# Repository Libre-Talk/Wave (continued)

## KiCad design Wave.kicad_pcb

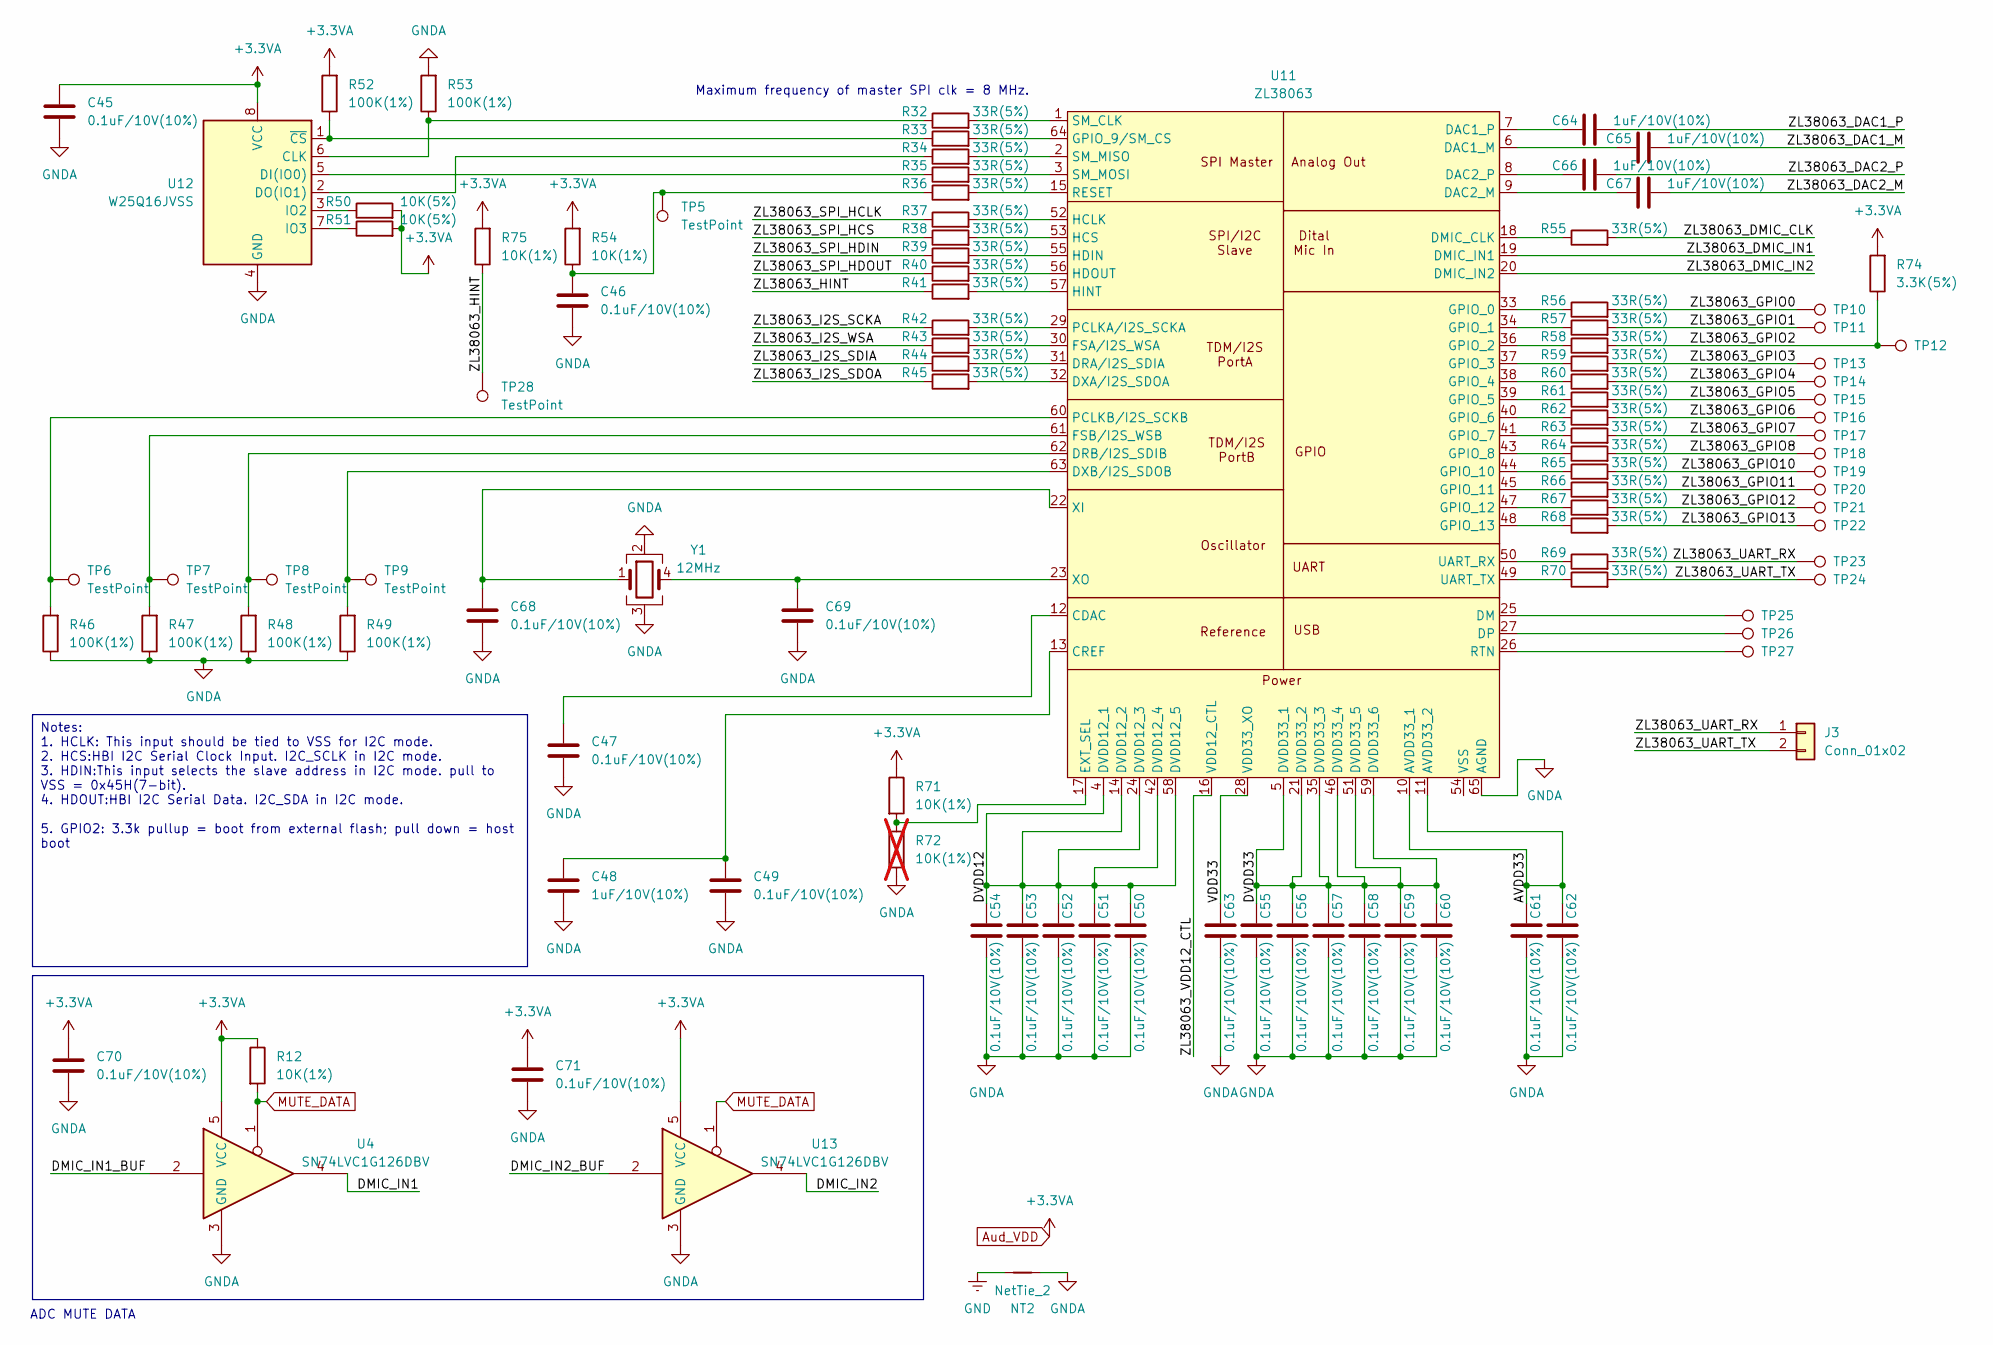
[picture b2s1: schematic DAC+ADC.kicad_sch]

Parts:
C45, C46, C47, C49, C50, C51, C52, C53, C54, C55, C56, C57, C58, C59, C60, C61, C62, C63, C68, C69, C70, C71: 0.1uF/10V(10%); C_0402_1005Metric
C48, C64, C65, C66, C67: 1uF/10V(10%); C_0402_1005Metric
J3: Conn_01x02; PinHeader_1x02_P2.54mm_Vertical
NT2: NetTie_2; NetTie-2_SMD_Pad0.5mm
R12, R54, R71, R75: 10K(1%); R_0402_1005Metric
R32, R33, R34, R35, R36, R37, R38, R39, R40, R41, R42, R43, R44, R45, R55, R56, R57, R58, R59, R60, R61, R62, R63, R64, R65, R66, R67, R68, R69, R70: 33R(5%); R_0402_1005Metric
R46, R47, R48, R49, R52, R53: 100K(1%); R_0402_1005Metric
R50, R51: 10K(5%); R_0402_1005Metric
R72: 10K(1%); R_0402_1005Metric; not fitted
R74: 3.3K(5%); R_0402_1005Metric
TP5, TP6, TP7, TP8, TP9, TP10, TP11, TP12, TP13, TP14, TP15, TP16, TP17, TP18, TP19, TP20, TP21, TP22, TP23, TP24, TP25, TP26, TP27, TP28: TestPoint; TestPoint_Pad_D1.0mm
U4, U13: SN74LVC1G126DBV; SOT-23-5
U11: ZL38063; QFN-64-1EP_9x9mm_P0.5mm_EP7.3x7.3mm_ThermalVias
U12: W25Q16JVSS; SOIC-8_3.9x4.9mm_P1.27mm
Y1: 12MHz; Crystal_SMD_2520-4Pin_2.5x2.0mm

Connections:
/DAC+ADC/AVDD33: C61.1, C62.1, U11.10 (AVDD33_1), U11.11 (AVDD33_2)
/DAC+ADC/DMIC_IN1: U4.4
/DAC+ADC/DMIC_IN1_BUF: U4.2
/DAC+ADC/DMIC_IN2: U13.4
/DAC+ADC/DMIC_IN2_BUF: U13.2
/DAC+ADC/DVDD12: C50.1, C51.1, C52.1, C53.1, C54.1, U11.4 (DVDD12_1), U11.14 (DVDD12_2), U11.24 (DVDD12_3), U11.42 (DVDD12_4), U11.58 (DVDD12_5)
/DAC+ADC/DVDD33: C55.1, C56.1, C57.1, C58.1, C59.1, C60.1, U11.5 (DVDD33_1), U11.21 (DVDD33_2), U11.35 (DVDD33_3), U11.46 (DVDD33_4), U11.51 (DVDD33_5), U11.59 (DVDD33_6)
/DAC+ADC/VDD33: C63.1, U11.28 (VDD33_XO)
/DAC+ADC/ZL38063_DAC1_M: C65.2
/DAC+ADC/ZL38063_DAC1_P: C64.2
/DAC+ADC/ZL38063_DAC2_M: C67.2
/DAC+ADC/ZL38063_DAC2_P: C66.2
/DAC+ADC/ZL38063_DMIC_CLK: R55.2
/DAC+ADC/ZL38063_DMIC_IN1: U11.19 (DMIC_IN1)
/DAC+ADC/ZL38063_DMIC_IN2: U11.20 (DMIC_IN2)
/DAC+ADC/ZL38063_GPIO0: R56.2, TP10.1
/DAC+ADC/ZL38063_GPIO1: R57.2, TP11.1
/DAC+ADC/ZL38063_GPIO2: R58.2, R74.1, TP12.1
/DAC+ADC/ZL38063_GPIO3: R59.2, TP13.1
/DAC+ADC/ZL38063_GPIO4: R60.2, TP14.1
/DAC+ADC/ZL38063_GPIO5: R61.2, TP15.1
/DAC+ADC/ZL38063_GPIO6: R62.2, TP16.1
/DAC+ADC/ZL38063_GPIO7: R63.2, TP17.1
/DAC+ADC/ZL38063_GPIO8: R64.2, TP18.1
/DAC+ADC/ZL38063_GPIO10: R65.2, TP19.1
/DAC+ADC/ZL38063_GPIO11: R66.2, TP20.1
/DAC+ADC/ZL38063_GPIO12: R67.2, TP21.1
/DAC+ADC/ZL38063_GPIO13: R68.2, TP22.1
/DAC+ADC/ZL38063_HINT: R41.1, R75.1, TP28.1
/DAC+ADC/ZL38063_I2S_SCKA: R42.1
/DAC+ADC/ZL38063_I2S_SDIA: R44.1
/DAC+ADC/ZL38063_I2S_SDOA: R45.1
/DAC+ADC/ZL38063_I2S_WSA: R43.1
/DAC+ADC/ZL38063_SPI_HCLK: R37.1
/DAC+ADC/ZL38063_SPI_HCS: R38.1
/DAC+ADC/ZL38063_SPI_HDIN: R39.1
/DAC+ADC/ZL38063_SPI_HDOUT: R40.1
/DAC+ADC/ZL38063_UART_RX: J3.1, R69.2, TP23.1
/DAC+ADC/ZL38063_UART_TX: J3.2, R70.2, TP24.1
/DAC+ADC/ZL38063_VDD12_CTL: U11.16 (VDD12_CTL)
Aud_VDD: C45.1, C70.1, C71.1, R12.1, R50.2, R51.2, R52.2, R54.2, R71.1, R74.2, R75.2, U4.5 (VCC), U12.8 (VCC), U13.5 (VCC); also elsewhere on the board
GND: NT2.2; also elsewhere on the board
GNDA: C45.2, C46.2, C47.2, C48.2, C49.2, C50.2, C51.2, C52.2, C53.2, C54.2, C55.2, C56.2, C57.2, C58.2, C59.2, C60.2, C61.2, C62.2, C63.2, C68.2, C69.2, C70.2, C71.2, NT2.1, R46.1, R47.1, R48.1, R49.1, R53.2, R72.2, U4.3 (GND), U11.65 (AGND), U12.4 (GND), U13.3 (GND), Y1.2, Y1.3
MUTE_DATA: R12.2, U4.1, U13.1; also elsewhere on the board
unnamed: C46.1, R36.1, R54.1, TP5.1
unnamed: C47.1, U11.12 (CDAC)
unnamed: C48.1, C49.1, U11.13 (CREF)
unnamed: C65.1, U11.6 (DAC1_M)
unnamed: C64.1, U11.7 (DAC1_P)
unnamed: C67.1, U11.9 (DAC2_M)
unnamed: C66.1, U11.8 (DAC2_P)
unnamed: TP25.1, U11.25 (DM)
unnamed: R55.1, U11.18 (DMIC_CLK)
unnamed: TP26.1, U11.27 (DP)
unnamed: R44.2, U11.31 (DRA/I2S_SDIA)
unnamed: R48.2, TP8.1, U11.62 (DRB/I2S_SDIB)
unnamed: R45.2, U11.32 (DXA/I2S_SDOA)
unnamed: R49.2, TP9.1, U11.63 (DXB/I2S_SDOB)
unnamed: R71.2, R72.1, U11.17 (EXT_SEL)
unnamed: R43.2, U11.30 (FSA/I2S_WSA)
unnamed: R47.2, TP7.1, U11.61 (FSB/I2S_WSB)
unnamed: R56.1, U11.33 (GPIO_0)
unnamed: R57.1, U11.34 (GPIO_1)
unnamed: R58.1, U11.36 (GPIO_2)
unnamed: R59.1, U11.37 (GPIO_3)
unnamed: R60.1, U11.38 (GPIO_4)
unnamed: R61.1, U11.39 (GPIO_5)
unnamed: R62.1, U11.40 (GPIO_6)
unnamed: R63.1, U11.41 (GPIO_7)
unnamed: R64.1, U11.43 (GPIO_8)
unnamed: R33.2, U11.64 (GPIO_9/SM_CS)
unnamed: R65.1, U11.44 (GPIO_10)
unnamed: R66.1, U11.45 (GPIO_11)
unnamed: R67.1, U11.47 (GPIO_12)
unnamed: R68.1, U11.48 (GPIO_13)
unnamed: R37.2, U11.52 (HCLK)
unnamed: R38.2, U11.53 (HCS)
unnamed: R39.2, U11.55 (HDIN)
unnamed: R40.2, U11.56 (HDOUT)
unnamed: R41.2, U11.57 (HINT)
unnamed: R42.2, U11.29 (PCLKA/I2S_SCKA)
unnamed: R46.2, TP6.1, U11.60 (PCLKB/I2S_SCKB)
unnamed: R36.2, U11.15 (RESET)
unnamed: TP27.1, U11.26 (RTN)
unnamed: R32.2, U11.1 (SM_CLK)
unnamed: R34.2, U11.2 (SM_MISO)
unnamed: R35.2, U11.3 (SM_MOSI)
unnamed: R69.1, U11.50 (UART_RX)
unnamed: R70.1, U11.49 (UART_TX)
unnamed: C68.1, U11.22 (XI), Y1.1
unnamed: C69.1, U11.23 (XO), Y1.4
unnamed: R32.1, R53.1, U12.6 (CLK)
unnamed: R35.1, U12.5 (DI(IO0))
unnamed: R34.1, U12.2 (DO(IO1))
unnamed: R50.1, U12.3 (IO2)
unnamed: R51.1, U12.7 (IO3)
unnamed: R33.1, R52.1, U12.1 (~CS)

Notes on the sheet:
Notes: 1. HCLK: This input should be tied to VSS for I2C mode. 2. HCS:HBI I2C Serial Clock Input. I2C_SCLK in I2C mode. 3. HDIN:This input selects the slave address in I2C mode. pull to VSS = 0x45H(7-bit). 4. HDOUT:HBI I2C Serial Data. I2C_SDA in I2C mode. 5. GPIO2: 3.3k pullup = boot from external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
Maximum frequency of master SPI clk = 8 MHz.
ADC MUTE DATA

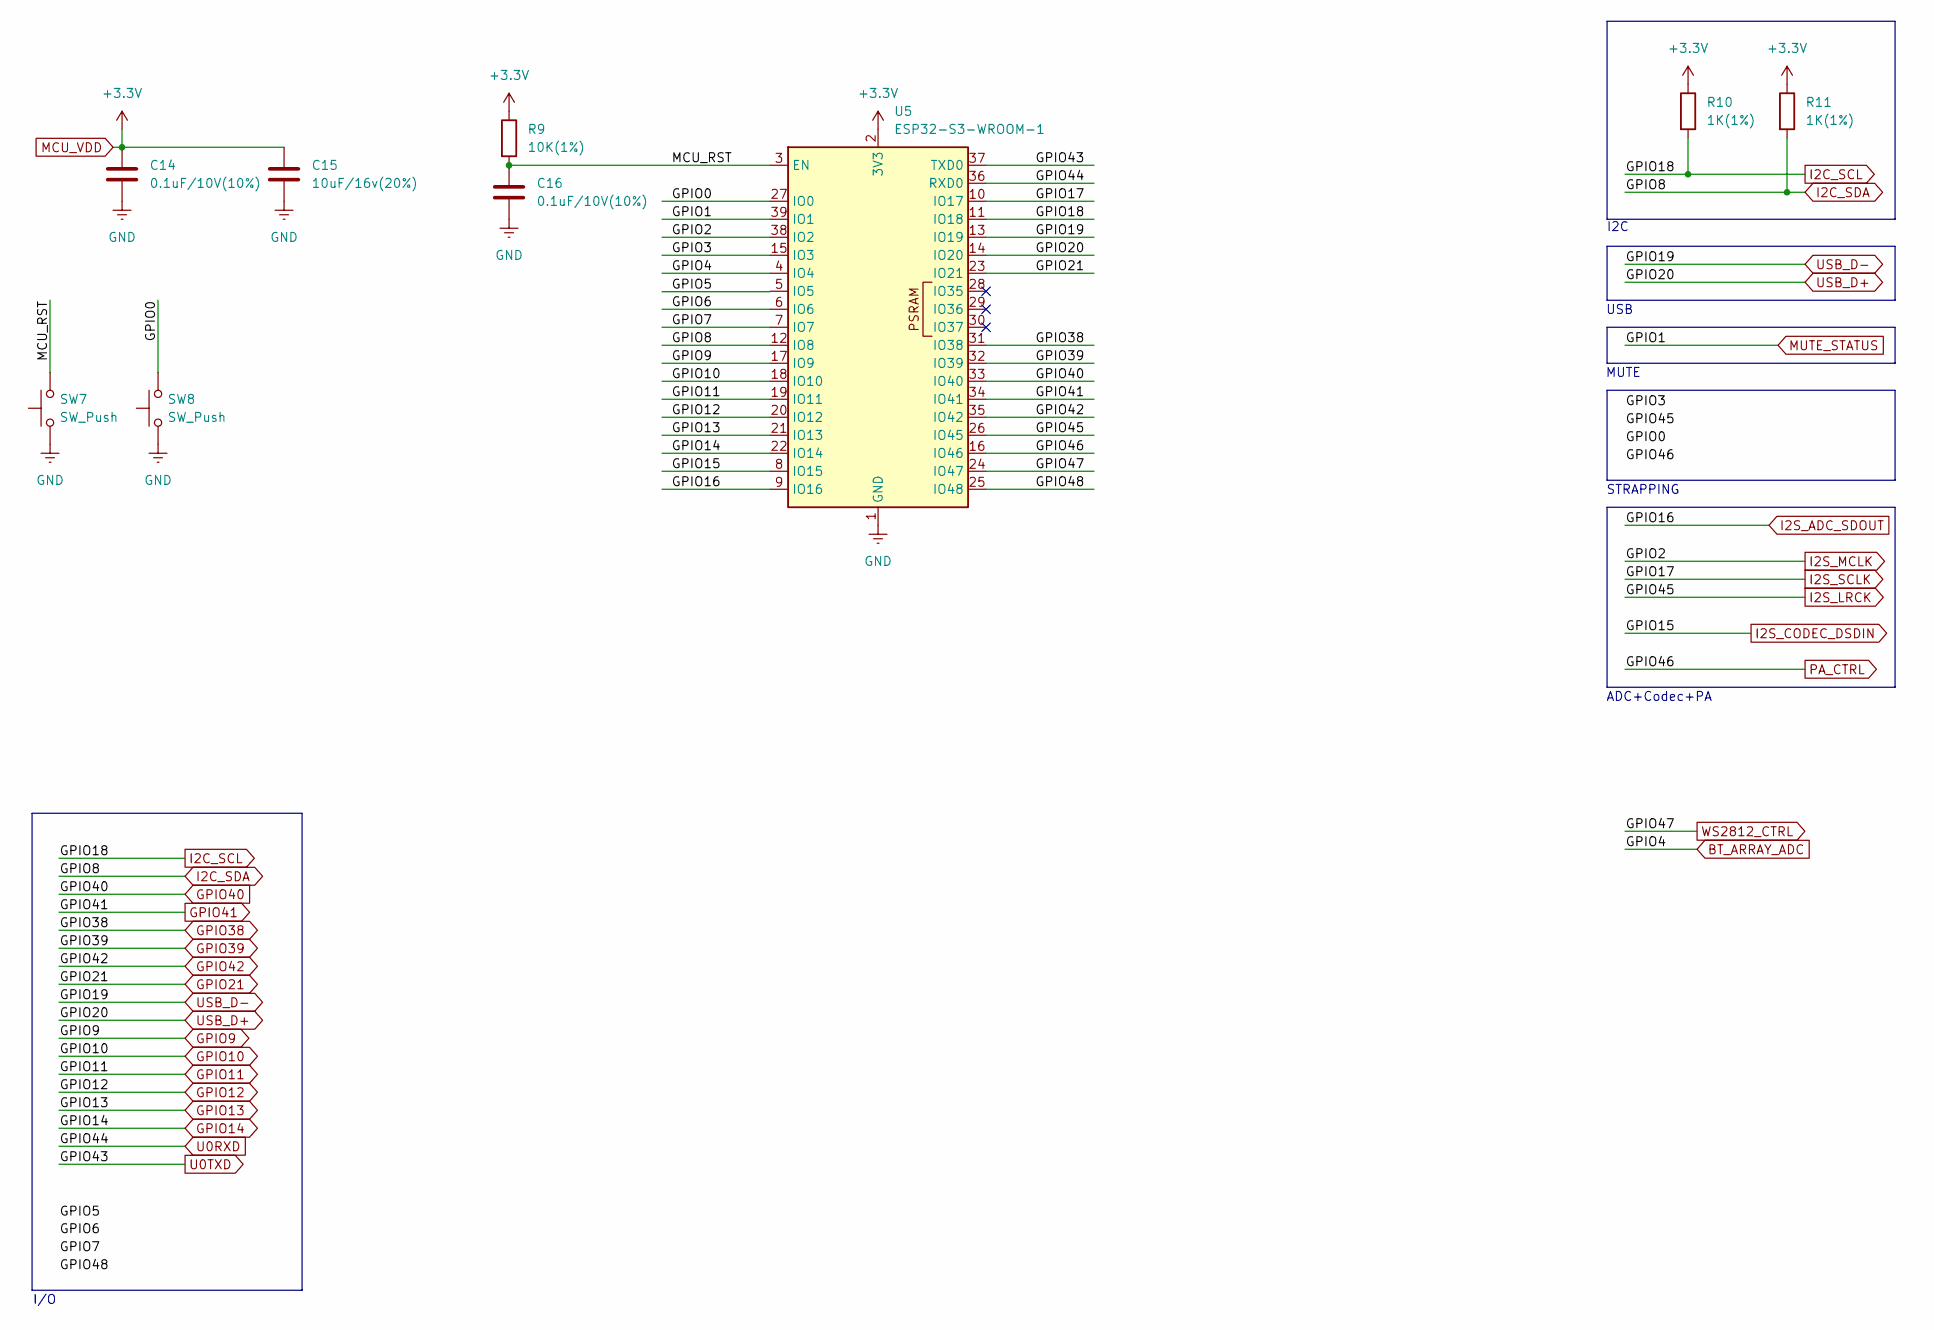
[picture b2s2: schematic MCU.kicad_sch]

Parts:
C14, C16: 0.1uF/10V(10%); C_0402_1005Metric
C15: 10uF/16v(20%); C_0402_1005Metric
R9: 10K(1%); R_0402_1005Metric
R10, R11: 1K(1%); R_0402_1005Metric
SW7, SW8: SW_Push; SW_SPST_PTS645
U5: ESP32-S3-WROOM-1

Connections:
/MCU/GPIO0: SW8.2, U5.27 (IO0)
/MCU/GPIO3: U5.15 (IO3)
/MCU/GPIO6: U5.6 (IO6)
/MCU/GPIO7: U5.7 (IO7)
/MCU/GPIO48: U5.25 (IO48)
/MCU/MCU_RST: C16.1, R9.2, SW7.2, U5.3 (EN)
BT_ARRAY_ADC: U5.4 (IO4); also elsewhere on the board
GND: C14.2, C15.2, C16.2, SW7.1, SW8.1, U5.1 (GND), U5.40 (GND), U5.41 (GND); also elsewhere on the board
GPIO9: U5.17 (IO9)
GPIO10: U5.18 (IO10)
GPIO11: U5.19 (IO11)
GPIO12: U5.20 (IO12)
GPIO13: U5.21 (IO13)
GPIO14: U5.22 (IO14)
GPIO21: U5.23 (IO21)
GPIO38: U5.31 (IO38)
GPIO39: U5.32 (IO39)
GPIO40: U5.33 (IO40)
GPIO41: U5.34 (IO41)
GPIO42: U5.35 (IO42)
I2C_SCL: R10.2, U5.11 (IO18); also elsewhere on the board
I2C_SDA: R11.2, U5.12 (IO8); also elsewhere on the board
I2S_ADC_SDOUT: U5.9 (IO16)
I2S_CODEC_DSDIN: U5.8 (IO15)
I2S_LRCK: U5.26 (IO45)
I2S_MCLK: U5.38 (IO2)
I2S_SCLK: U5.10 (IO17)
MCU_VDD: C14.1, C15.1, R9.1, R10.1, R11.1, U5.2 (3V3); also elsewhere on the board
MUTE_DATA: U5.39 (IO1); also elsewhere on the board
PA_CTRL: U5.16 (IO46); also elsewhere on the board
U0RXD: U5.36 (RXD0)
U0TXD: U5.37 (TXD0)
USB_D+: U5.14 (IO20); also elsewhere on the board
USB_D-: U5.13 (IO19); also elsewhere on the board
WS2812_CTRL: U5.24 (IO47); also elsewhere on the board

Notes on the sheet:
MUTE
ADC+Codec+PA
I/O
USB
STRAPPING
I2C

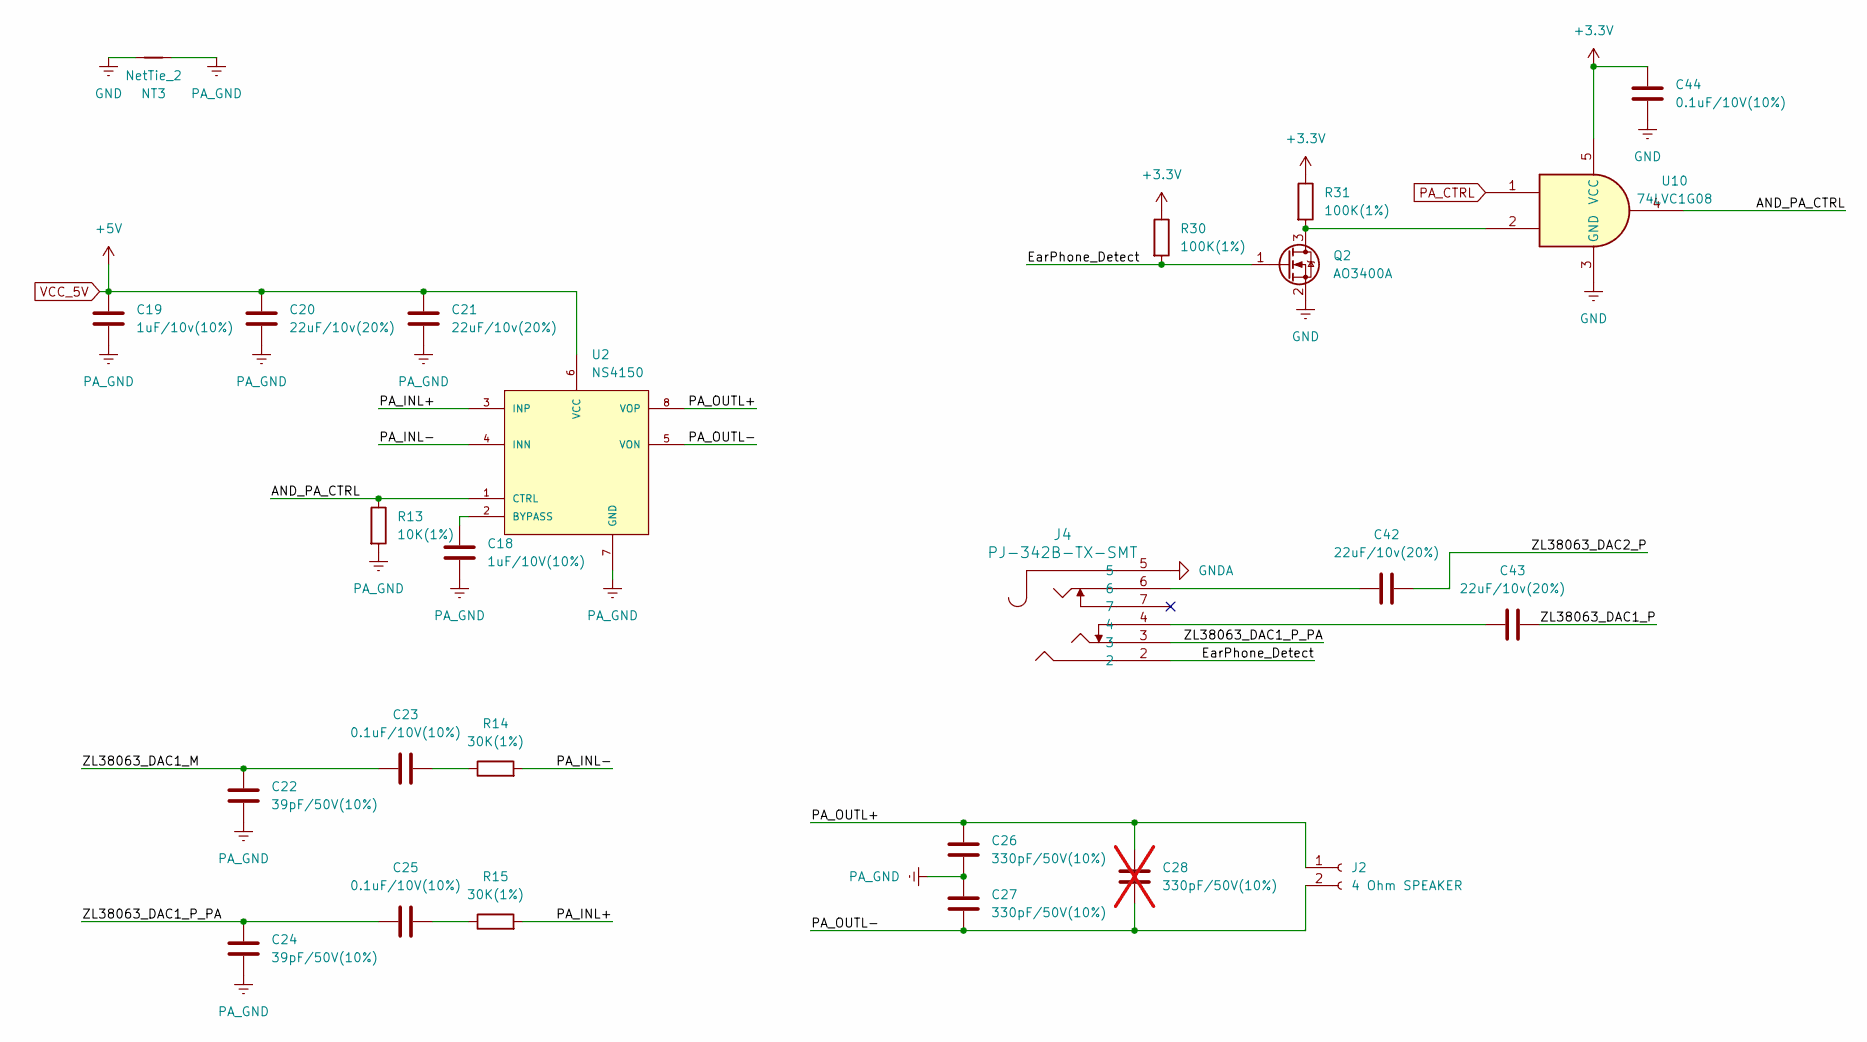
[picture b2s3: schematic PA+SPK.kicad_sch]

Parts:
C18: 1uF/10V(10%); C_0402_1005Metric
C19: 1uF/10v(10%); C_0402_1005Metric
C20, C21, C42, C43: 22uF/10v(20%); C_0402_1005Metric
C22, C24: 39pF/50V(10%); C_0402_1005Metric
C23, C25, C44: 0.1uF/10V(10%); C_0402_1005Metric
C26, C27: 330pF/50V(10%); C_0402_1005Metric
C28: 330pF/50V(10%); C_0402_1005Metric; not fitted
J2: 4 Ohm SPEAKER; JST_PH_B2B-PH-K_1x02_P2.00mm_Vertical
J4: PJ-342B-TX-SMT; PJ-342B-TX-SMT_XKB
NT3: NetTie_2; NetTie-2_SMD_Pad0.5mm
Q2: AO3400A; SOT-23
R13: 10K(1%); R_0402_1005Metric
R14, R15: 30K(1%); R_0402_1005Metric
R30, R31: 100K(1%); R_0402_1005Metric
U2: NS4150; MSOP-8_3x3mm_P0.65mm
U10: 74LVC1G08; SOT-23-5

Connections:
/PA & Speaker/AND_PA_CTRL: R13.1, U2.1 (CTRL), U10.4
/PA & Speaker/EarPhone_Detect: J4.2, Q2.1 (G), R30.2
/PA & Speaker/PA_INL+: R15.2, U2.3 (INP)
/PA & Speaker/PA_INL-: R14.2, U2.4 (INN)
/PA & Speaker/PA_OUTL+: C26.1, C28.1, J2.1, U2.8 (VOP)
/PA & Speaker/PA_OUTL-: C27.2, C28.2, J2.2, U2.5 (VON)
/PA & Speaker/ZL38063_DAC1_M: C22.1, C23.1
/PA & Speaker/ZL38063_DAC1_P: C43.2
/PA & Speaker/ZL38063_DAC1_P_PA: C24.1, C25.1, J4.3
/PA & Speaker/ZL38063_DAC2_P: C42.2
GND: C44.1, NT3.2, Q2.2 (S), U10.3 (GND); also elsewhere on the board
MCU_VDD: C44.2, R30.1, R31.1, U10.5 (VCC); also elsewhere on the board
unnamed: C23.2, R14.1
unnamed: C25.2, R15.1
unnamed: C42.1, J4.6
unnamed: C43.1, J4.4
unnamed: Q2.3 (D), R31.2, U10.2
unnamed: C18.1, U2.2 (BYPASS)
PA_CTRL: U10.1; also elsewhere on the board
PA_GND: C18.2, C19.2, C20.2, C21.2, C22.2, C24.2, C26.2, C27.1, NT3.1, R13.2, U2.7 (GND)
VCC_5V: C19.1, C20.1, C21.1, U2.6 (VCC); also elsewhere on the board

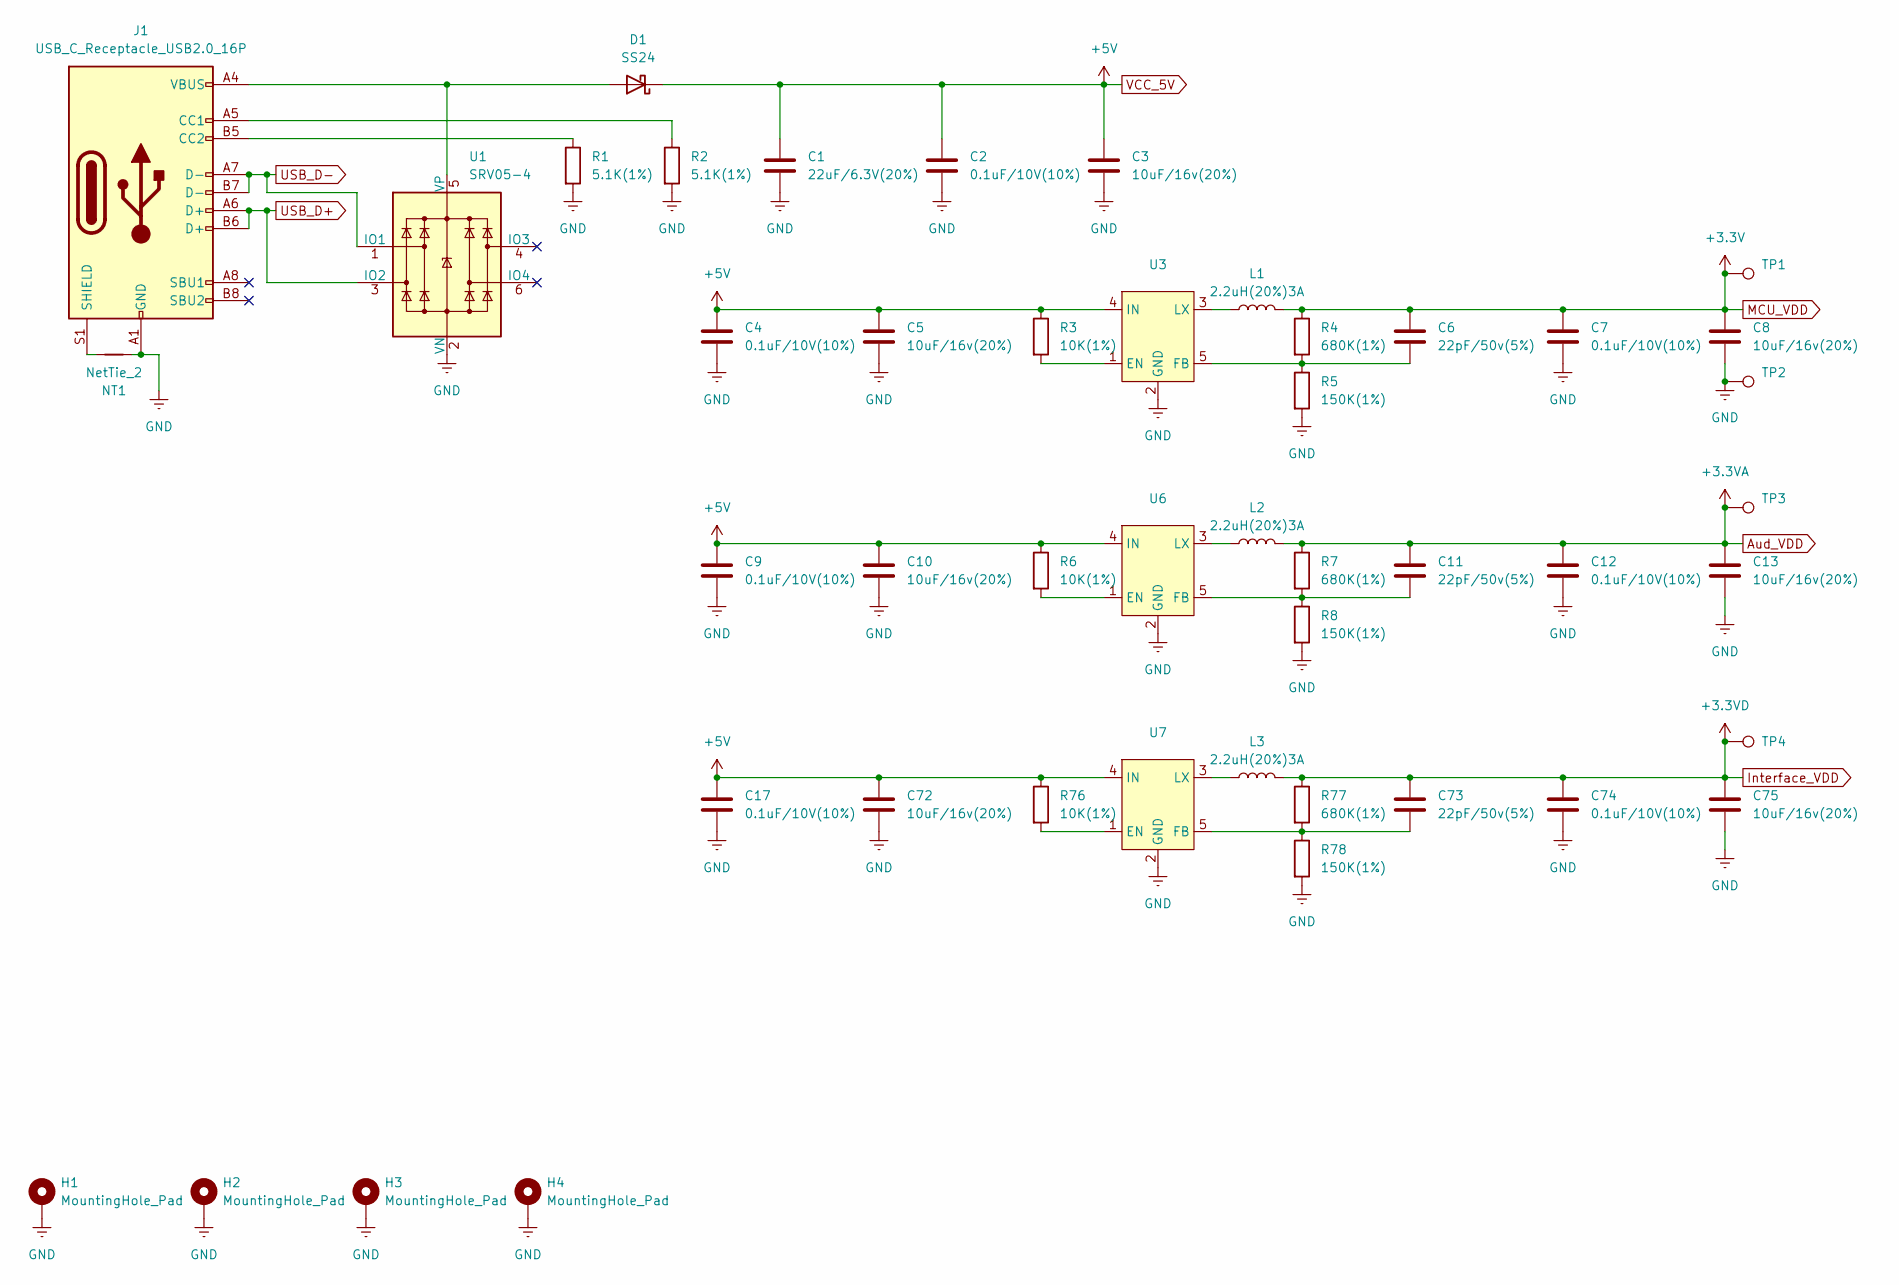
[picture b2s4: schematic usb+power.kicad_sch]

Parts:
C1: 22uF/6.3V(20%); C_0402_1005Metric
C2, C4, C7, C9, C12, C17, C74: 0.1uF/10V(10%); C_0402_1005Metric
C3, C5, C8, C10, C13, C72, C75: 10uF/16v(20%); C_0402_1005Metric
C6, C11, C73: 22pF/50v(5%); C_0402_1005Metric
D1: SS24; D_SMA
H1, H2, H3, H4: MountingHole_Pad; MountingHole_3.2mm_M3_Pad_Via
J1: USB_C_Receptacle_USB2.0_16P; USB_C_Receptacle_G-Switch_GT-USB-7010ASV
L1, L2, L3: 2.2uH(20%)3A; L_0603_1608Metric
NT1: NetTie_2; NetTie-2_SMD_Pad0.5mm
R1, R2: 5.1K(1%); R_0402_1005Metric
R3, R6, R76: 10K(1%); R_0402_1005Metric
R4, R7, R77: 680K(1%); R_0402_1005Metric
R5, R8, R78: 150K(1%); R_0402_1005Metric
TP1, TP2, TP3, TP4: TestPoint; TestPoint_Pad_D1.0mm
U1: SRV05-4; SOT-23-6
U3, U6, U7: SOT-23-5

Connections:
Aud_VDD: C11.1, C12.1, C13.1, L2.2, R7.1, TP3.1; also elsewhere on the board
GND: C1.2, C2.2, C3.2, C4.2, C5.2, C7.2, C8.2, C9.2, C10.2, C12.2, C13.2, C17.2, C72.2, C74.2, C75.2, H1.1, H2.1, H3.1, H4.1, J1.A1 (GND), J1.A12 (GND), J1.B1 (GND), J1.B12 (GND), NT1.1, R1.2, R2.2, R5.2, R8.2, R78.2, TP2.1, U1.2 (VN), U3.2 (GND), U6.2 (GND), U7.2 (GND); also elsewhere on the board
Interface_VDD: C73.1, C74.1, C75.1, L3.2, R77.1, TP4.1; also elsewhere on the board
MCU_VDD: C6.1, C7.1, C8.1, L1.2, R4.1, TP1.1; also elsewhere on the board
unnamed: D1.2 (A), J1.A4 (VBUS), J1.A9 (VBUS), J1.B4 (VBUS), J1.B9 (VBUS), U1.5 (VP)
unnamed: J1.A5 (CC1), R2.1
unnamed: J1.B5 (CC2), R1.1
unnamed: J1.S1 (SHIELD), NT1.2
unnamed: R3.2, U3.1 (EN)
unnamed: C6.2, R4.2, R5.1, U3.5 (FB)
unnamed: L1.1, U3.3 (LX)
unnamed: R6.2, U6.1 (EN)
unnamed: C11.2, R7.2, R8.1, U6.5 (FB)
unnamed: L2.1, U6.3 (LX)
unnamed: R76.2, U7.1 (EN)
unnamed: C73.2, R77.2, R78.1, U7.5 (FB)
unnamed: L3.1, U7.3 (LX)
USB_D+: J1.A6 (D+), J1.B6 (D+), U1.3 (IO2); also elsewhere on the board
USB_D-: J1.A7 (D-), J1.B7 (D-), U1.1 (IO1); also elsewhere on the board
VCC_5V: C1.1, C2.1, C3.1, C4.1, C5.1, C9.1, C10.1, C17.1, C72.1, D1.1 (K), R3.1, R6.1, R76.1, U3.4 (IN), U6.4 (IN), U7.4 (IN); also elsewhere on the board

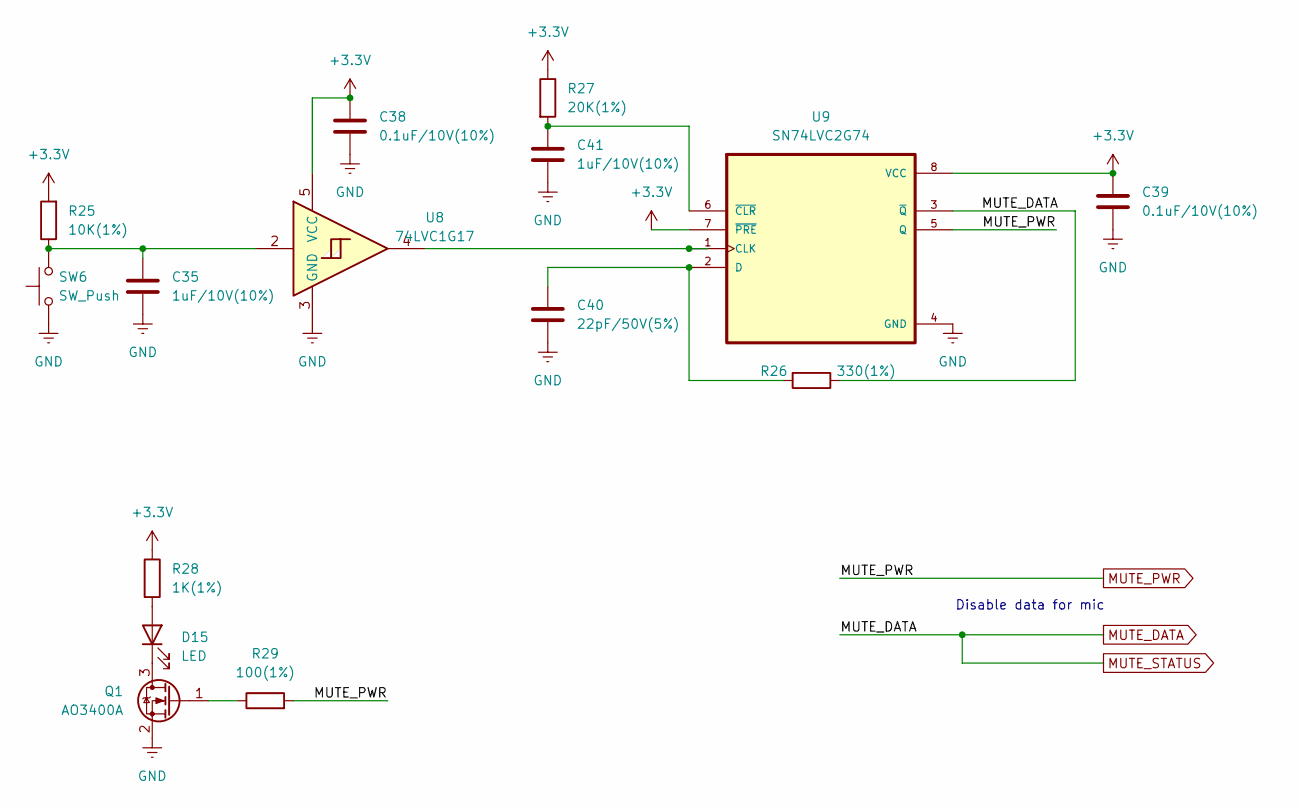
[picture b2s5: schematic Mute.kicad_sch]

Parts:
C35, C41: 1uF/10V(10%); C_0402_1005Metric
C38, C39: 0.1uF/10V(10%); C_0402_1005Metric
C40: 22pF/50V(5%); C_0402_1005Metric
D15: LED; LED_0603_1608Metric
Q1: AO3400A; SOT-23
R25: 10K(1%); R_0402_1005Metric
R26: 330(1%); R_0402_1005Metric
R27: 20K(1%); R_0402_1005Metric
R28: 1K(1%); R_0402_1005Metric
R29: 100(1%); R_0402_1005Metric
SW6: SW_Push; SW_SPST_PTS645
U8: 74LVC1G17; SOT-23-5
U9: SN74LVC2G74; VSSOP-8_2.4x2.1mm_P0.5mm

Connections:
GND: C35.2, C38.2, C39.2, C40.2, C41.2, Q1.2 (S), SW6.1, U8.3 (GND), U9.4 (GND); also elsewhere on the board
MCU_VDD: C38.1, C39.1, R25.2, R27.1, R28.1, U8.5 (VCC), U9.7 (~PRE), U9.8 (VCC); also elsewhere on the board
MUTE_DATA: R26.1, U9.3 (~Q); also elsewhere on the board
MUTE_PWR: R29.2, U9.5 (Q)
unnamed: C35.1, R25.1, SW6.2, U8.2
unnamed: D15.2 (A), R28.2
unnamed: D15.1 (K), Q1.3 (D)
unnamed: Q1.1 (G), R29.1
unnamed: U8.4, U9.1 (CLK)
unnamed: C40.1, R26.2, U9.2 (D)
unnamed: C41.1, R27.2, U9.6 (~CLR)

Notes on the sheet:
Disable data for mic

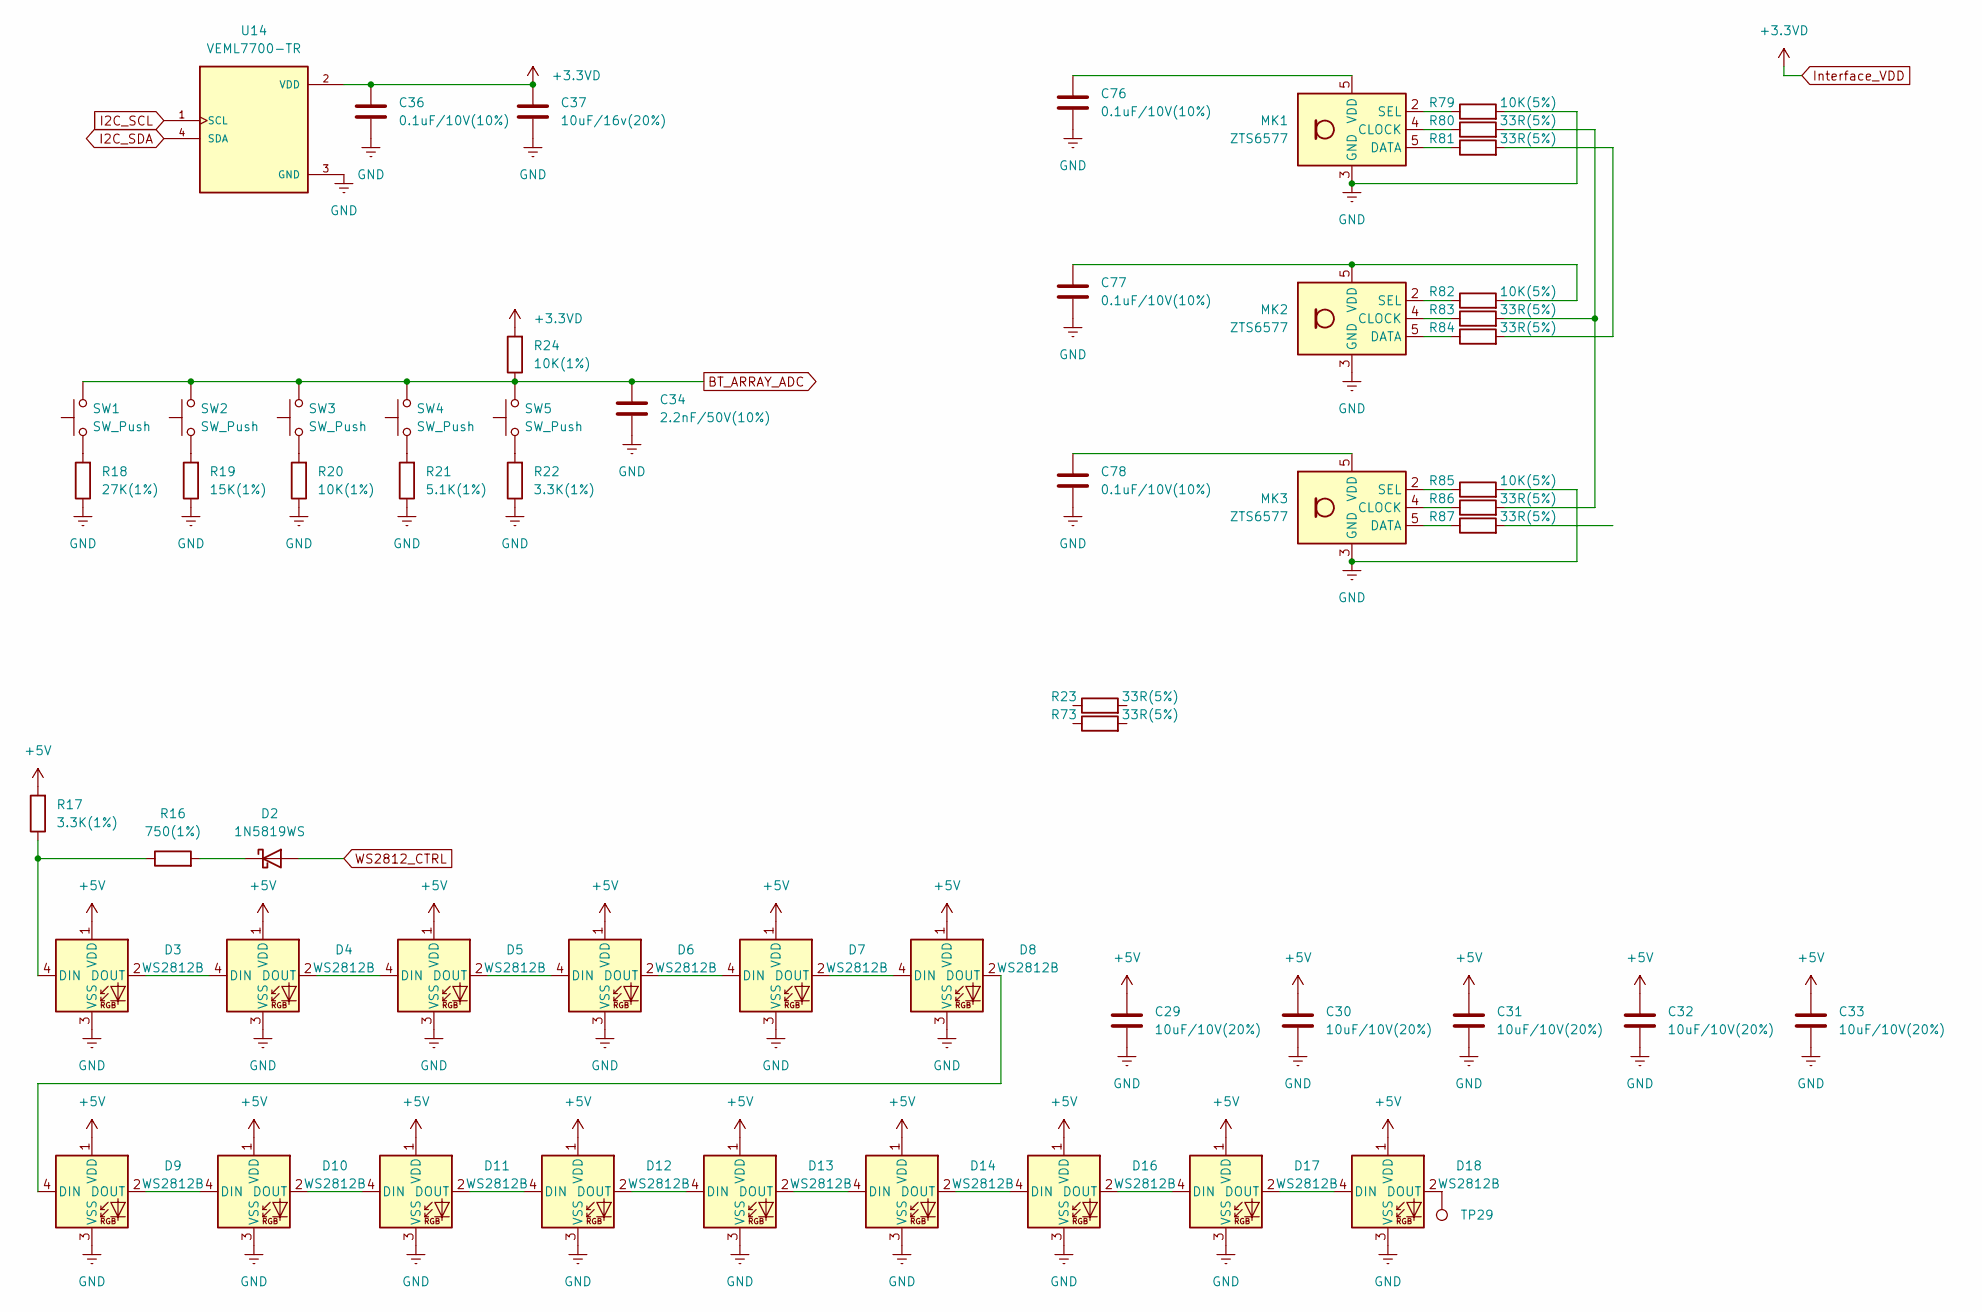
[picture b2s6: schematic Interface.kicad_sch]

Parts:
C29, C30, C31, C32, C33: 10uF/10V(20%); C_0402_1005Metric
C34: 2.2nF/50V(10%); C_0402_1005Metric
C36, C76, C77, C78: 0.1uF/10V(10%); C_0402_1005Metric
C37: 10uF/16v(20%); C_0402_1005Metric
D2: 1N5819WS; D_SOD-323
D3, D4, D5, D6, D7, D8, D9, D10, D11, D12, D13, D14, D16, D17, D18: WS2812B; LED_WS2812B_PLCC4_5.0x5.0mm_P3.2mm
MK1, MK2, MK3: ZTS6577; Knowles_LGA-5_3.5x2.65mm
R16: 750(1%); R_0402_1005Metric
R17, R22: 3.3K(1%); R_0402_1005Metric
R18: 27K(1%); R_0402_1005Metric
R19: 15K(1%); R_0402_1005Metric
R20, R24: 10K(1%); R_0402_1005Metric
R21: 5.1K(1%); R_0402_1005Metric
R23, R73, R80, R81, R83, R84, R86, R87: 33R(5%); R_0402_1005Metric
R79, R82, R85: 10K(5%); R_0402_1005Metric
SW1, SW2, SW3, SW4, SW5: SW_Push; SW_SPST_PTS645
TP29: TestPoint; TestPoint_Pad_D1.0mm
U14: VEML7700-TR; XDCR_VEML7700-TR; PARTREV 1.6

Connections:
BT_ARRAY_ADC: C34.1, R24.1, SW1.2, SW2.2, SW3.2, SW4.2, SW5.2; also elsewhere on the board
GND: C29.2, C30.2, C31.2, C32.2, C33.2, C34.2, C36.2, C37.2, C76.2, C77.2, C78.2, D3.3 (VSS), D4.3 (VSS), D5.3 (VSS), D6.3 (VSS), D7.3 (VSS), D8.3 (VSS), D9.3 (VSS), D10.3 (VSS), D11.3 (VSS), D12.3 (VSS), D13.3 (VSS), D14.3 (VSS), D16.3 (VSS), D17.3 (VSS), D18.3 (VSS), MK1.3 (GND), MK2.3 (GND), MK3.3 (GND), R18.1, R19.1, R20.1, R21.1, R22.1, R79.2, R85.2, U14.3 (GND); also elsewhere on the board
I2C_SCL: U14.1 (SCL); also elsewhere on the board
I2C_SDA: U14.4 (SDA); also elsewhere on the board
Interface_VDD: C36.1, C37.1, R24.2, U14.2 (VDD); also elsewhere on the board
unnamed: D2.1 (K), R16.2
unnamed: D3.4 (DIN), R16.1, R17.1
unnamed: D3.2 (DOUT), D4.4 (DIN)
unnamed: D4.2 (DOUT), D5.4 (DIN)
unnamed: D5.2 (DOUT), D6.4 (DIN)
unnamed: D6.2 (DOUT), D7.4 (DIN)
unnamed: D7.2 (DOUT), D8.4 (DIN)
unnamed: D8.2 (DOUT), D9.4 (DIN)
unnamed: D9.2 (DOUT), D10.4 (DIN)
unnamed: D10.2 (DOUT), D11.4 (DIN)
unnamed: D11.2 (DOUT), D12.4 (DIN)
unnamed: D12.2 (DOUT), D13.4 (DIN)
unnamed: D13.2 (DOUT), D14.4 (DIN)
unnamed: D14.2 (DOUT), D16.4 (DIN)
unnamed: D16.2 (DOUT), D17.4 (DIN)
unnamed: D17.2 (DOUT), D18.4 (DIN)
unnamed: D18.2 (DOUT), TP29.1
unnamed: MK1.4 (CLOCK), R80.1
unnamed: MK1.2 (SEL), R79.1
unnamed: MK2.4 (CLOCK), R83.1
unnamed: MK2.2 (SEL), R82.1
unnamed: MK3.4 (CLOCK), R86.1
unnamed: MK3.2 (SEL), R85.1
unnamed: R18.2, SW1.1
unnamed: R19.2, SW2.1
unnamed: R20.2, SW3.1
unnamed: R21.2, SW4.1
unnamed: R22.2, SW5.1
unnamed: R80.2, R83.2, R86.2
unnamed: R81.2, R84.2
VCC_5V: C29.1, C30.1, C31.1, C32.1, C33.1, D3.1 (VDD), D4.1 (VDD), D5.1 (VDD), D6.1 (VDD), D7.1 (VDD), D8.1 (VDD), D9.1 (VDD), D10.1 (VDD), D11.1 (VDD), D12.1 (VDD), D13.1 (VDD), D14.1 (VDD), D16.1 (VDD), D17.1 (VDD), D18.1 (VDD), R17.2; also elsewhere on the board
WS2812_CTRL: D2.2 (A); also elsewhere on the board

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
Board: 4 copper layers, 253 parts (24 on the bottom side), 157 nets, no tracks yet.

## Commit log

2024-03-22 Update LICENSE
2024-03-22 Added overview image
2024-03-22 Initial population of PCB
2024-03-23 Added DSP, Neopixles, MIC's and mounting holes
2024-03-25 Added lock files to GitIgnore
2024-04-05 Split boards and schematics to Top, Main and Bottom
2024-04-06 Full routed and DRC completed
2024-04-06 Added 3.5mm Jack to top board
2024-04-06 Cleanup and naming of Touchpoints
2024-04-06 Silkscreen text alignment
